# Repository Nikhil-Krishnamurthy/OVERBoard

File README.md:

# OVERBoard
This is my attempt at creating a custom keyboard with several unique features, this has a layer system that I have modified to work with specific tasks on my pc, I also have a 2.8 in screen to display custom text, ui, and macros. There is a full 78 led matrix, dual pi pico system, and 3 rotary encoders that interface in this system.   
# Key Features   
Full TKL Keyboard Matrix   
4 Layer Keyboard System   
3 Encoders Interfacing with the Layer System   
78 Led Matrix system   
320 x 240 2.8 inch display   
Custom UI and layer switching menus   
Computer interface and data transmission   
Custom 5A power system   

## Onshape-link:
https://cad.onshape.com/documents/a6bd6c4e9013194f1dc31777/w/de360b55982ee6c60ca7c4d4/e/a374dba059f4ceb7d8e6600d?renderMode=0&uiState=6a4a7855afac9a027952f82f 

# Flashing      
Flashing is done through two steps, compiling the C qmk file through QMK MSYS to compile to a uf2 file, which then can be flashed to the pi pico through holding the bootsel button and plugging it in to the usb power. Then just upload the new uf2 file to the pi pico. To flash the pi pico 2 for the display, you have to download the entire folder of the custom c++, and then through a terminal of your choice compile it. (I use vs code and i got it to work through there, idk about others). Then upload the second uf2 file to the pi pico 2 by holding the bootsel button and uploading it there.

# BOM   
78 [3 Pin Mechanical Keyboard Switches   ](https://www.amazon.com/Leezmark-Mechanical-Dustproof-Replacement-Keyboards/dp/B0GV78B48N/ref=mp_s_a_1_20_sspa?crid=2GGAVKPX5GKH&dib=eyJ2IjoiMSJ9.BS9ZW8A40QZK6iI4UmdZkYcVp812RDtM8dzqQtxJq5kz5jddC0aGCLYpUDj6oWZM4geYAz7LL5dJKQJ_sMRCqYbuT9Zwzy20VnrTvVNVI-2PMGM8y_OT_gXPSKltVj0ZCmtBrzLAvtF8hVyPpS-bcG8HSGX4meJ7BWVw4GwyFBtzq-VV4k_-OB3_U29mYmabBNX5P_2u1xLUz0WsYM_SZg.sOaHXiIPD6Bd4c6RHFdcsiI9AAYZXd1oFGZit3XfvzE&dib_tag=se&keywords=mechanical+keyboard+switches&qid=1786102391&sprefix=mecha%2Caps%2C1667&sr=8-20-spons&xpid=P4xuzyhmO1Kis&sp_csd=d2lkZ2V0TmFtZT1zcF9waG9uZV9zZWFyY2hfbXRm&psc=1)   
78 [SK6812 Mini-E LEDs](https://www.amazon.com/Lizusidtsy-Similar-Individually-Addressable-500076361/dp/B0D62PYX62/ref=mp_s_a_1_10?crid=1HXPOB1FA28BI&dib=eyJ2IjoiMSJ9.9VtPip6eaOO1-XFGgh2XxRcv7goQ3zQpYu2U5s9L9nSHVgE9buEYKNyEW3iah_ciC9jxtcFWsezkLg6mPwawYLvC0YwcBautoxVQw8uHIajIIKaw2BAEOz0msTKg2i1JiFDcOfpwOktIFD5m-rM-sLH5aurg7jONQpTc9ztb7qjGY4VW4UKlHhBSvXDKLMnpFN1p0uSk9QlHmR1fMhQoKQ.cp7zFL1gJURH3RVmt4PrTOWDThkTRaVYkx8k7CsSdDU&dib_tag=se&keywords=sk6812+mini+e&qid=1786102738&s=industrial&sprefix=sk6812+mini+e%2Cindustrial%2C227&sr=1-10-catcorr)   
3 [EC11 Rotary encoders](https://www.amazon.com/CGNRONEAU-Potentiometer-Raspberry-Electronics-Projects/dp/B0G48Z8B9Q/ref=mp_s_a_1_5?crid=SJZ3ZTB60ZB5&dib=eyJ2IjoiMSJ9.DXj00Da7o69UiffMrM5wQRPYTBTu96F7xG_REVVFTXyDDE7Ct_VRsisag9rFMKgkTnHD1maKyGOHqHwwsa9QOm4nJbuxf-u1h8I8Xeu_QS-_GGyZhZ7IW7rUedH8wyPUQpJnUpBYRTrw7qkoa3L6uI7fxGQ1JdWoYiTZq1MJnh7YbKwp_SVgYWuv54q8JgQ_uJAa0EScvo-vtg_HxxVShA.oFRLtfeS884kGRJ9817n1MkEJusgqgWJDlI8D6AScFo&dib_tag=se&keywords=ec11+rotary+encoder&qid=1786102850&s=industrial&sprefix=ec11+rotary+encoder%2Cindustrial%2C296&sr=1-5)    
1 [Keycap Set](https://www.amazon.com/Womier-Doubleshot-Universal-Compatiability-Switches/dp/B0DD3MFZJH/ref=mp_s_a_1_4?dib=eyJ2IjoiMSJ9.NYb-M_oBXZ4sYXBFeumxLCGVNsY9r-6v4MP0X_NiII59u2l-eoBS-fSIwKjgQw8UQnKp5aItpglhW1_vmJ5Zi3Ai9TdxAWYqoLRUdImCShzhl38JPSy1eJCwtC9gqwE5WcnlIVPYZwyoVEbIaEuOxTBP47_ipk5BJsu7sIIcEQwtiRsUoIT2AKQ4hwcLJanAgVfd3swCPsz1cHzkkB3fEA.LHY6OJX_2Vt0jXq0Am2Od0HAyrY-O1Iw68TDGDFU8LQ&dib_tag=se&keywords=keycap+set&qid=1786102952&sr=8-4)   
1 [Stabilizer Set](https://www.amazon.com/DUROCK-Stabilizers-Translucent-Keyboard-Mechanical/dp/B0B2RVN19F/ref=mp_s_a_1_1?crid=RUCGVW5PCSL7&dib=eyJ2IjoiMSJ9.FUE_jABwKLA1OASEMhZRJdxEw5T6Pmde5A4peNgmaHbFq5e1Nyw0ducx_W87F-YdPvY6Z0F0Ws9Z5KWRT10otnbc7i3mqQ-KSsT8q0_UoKFDrMQOU2Zr7UFsQVD8SH_3jzvns1ANBC4ikHp7kZKjsS9mrpaVKSuOX6QgBT75oK6L6rT38cDrAPZf1bMy2eiDNbRMvr3UK6Jnu7D304s7ww.Ds4MVNaTUXEreelnZ5y9dkQEI_1UVwucidZDuxVlDSo&dib_tag=se&keywords=keyboard+stabilizer+pcb+mount&qid=1786103068&sprefix=keyboard+stabilizer+pcb+moun%2Cpc%2C281&sr=8-1)   
10 [0.1uF SMD 0805 Capacitors](https://www.digikey.com/en/products/detail/samsung-electro-mechanics/CL21B104KBCNNNC/3886661)   
2 [10uF SMD 1206 Capacitors](https://www.digikey.com/en/products/detail/taiyo-yuden/TMK316BJ106ML-T/1172143)   
83 [Through Hole Diodes](https://www.digikey.com/en/products/detail/onsemi/1N4148TR/458811)   
1 [Raspberry Pi Pico](https://www.digikey.com/en/products/detail/raspberry-pi/SC0915/13624793)   
1 [Raspberry Pi Pico 2](https://www.digikey.com/en/products/detail/raspberry-pi/SC1631/24627136)   
1 [SN74HCT245PWR](https://www.digikey.com/en/products/detail/texas-instruments/SN74HCT245PWR/376998)   
1 [Mini 560 5A 5V](https://www.amazon.com/ACEIRMC-Efficiency-Converter-Regulator-Stabilized/dp/B0C98GN9R5/ref=mp_s_a_1_4?crid=2AVG7EVJEY2B9&dib=eyJ2IjoiMSJ9.YQJnYbrVm2KfCwo1WAsOv_9mCXY0p27qXY_bAWcHnAztXAalke-6x_LLhC_8PmYHInSFxohDrh9t3UeH3i8bvUFj-epQ0_xXJwlrhhlWOhZJfog3TIgcDjFTwO7dwkMsRUWsBu6tSt_Lye0NUieFGLgw9ekInTt2RbwoX9bJ0JOObYWOKjC2M1PCHkkIN_Ke.J03En0j60RIf0zi2gOz474K4xhu8YiPPLa1dOAJTqoU&dib_tag=se&keywords=mini+560+5v+5a&qid=1786103755&sprefix=mi%2Cpc%2C4329&sr=8-4)   
1 [Adafruit 5807 Power Evaluation Board](https://www.digikey.com/en/products/detail/adafruit-industries-llc/5807/21839778)   
1 [2.8 in 320 x 240 SPI Serial TFT display](https://www.amazon.com/DIANN-ILI9341-Display-320x240-Screen/dp/B0BNQBKFCT/ref=mp_s_a_1_4?crid=1IO0JMISFCIW5&dib=eyJ2IjoiMSJ9.QdQv9Z60xKItFJyKtGDGVEe0E5DZHOpvSyDlzSsJM0ahxq3n0oBPRCWegDN5Bh4kMcEsYOjRE9r_6PQ-nRDFi45yabmboblZpYIfpVL-1wZ9Gbc-wRBgY9Q3zt3W4nQNGskA3h3qFBMzfNfbmmOG4S9Yv8aLMXAZH_x-N28DwhMUSRzU2xY8tLeu3uxt2kHptwfZuykGqU6NKyFsdJm3gw.irWclV9rp7JxQy7JeD-LQJ3wXUPrGnMFIF87TexXEg0&dib_tag=se&keywords=2.8+in+spi+display+color&qid=1786105121&s=industrial&sprefix=2.8+in+spi+display+color%2Cindustrial%2C196&sr=1-4)   
2 [PTS810_SJM_250](https://www.digikey.com/en/products/detail/c-k/PTS810SJK250SMTR-LFS/4176611)   
2 [4.7k SMD 0805 resistors](https://www.digikey.com/en/products/detail/panasonic-industry/ERA-6AEB472V/1465765)    
10 [10k SMD 0805 resistors](https://www.digikey.com/en/products/detail/stackpole-electronics-inc/RMCF0805FT10K0/1760676)   
## Extra Parts not part of BOM
9 [M3 Heat set inserts](https://www.amazon.com/HANGLIFE-Heat-Set-Threaded-Printing-Components/dp/B0CS6VZYL8/ref=mp_s_a_1_2_sspa?crid=2B6EZ44CM5F8W&dib=eyJ2IjoiMSJ9.64CwhAq2F4wt2J7X2RWpxsbGQNoHV8siDt0bl6JQWF52xU_4RhH0jdpfO7SRVfnWZU2jv3CI10a2JeWKff2m2wFIr10td08-ZNDs7jlZM_gW5mSgs-W56Qb0sIpuTAgPvamIXJbOre0ZmTZ6kXSKiIbGKsS7vC-VFf2Imqp2yVl_mDHaTy5djVOZQ_dIL6f3OuER50SkQsIQripMtAXk4A.KM8dXGX0d71WWG7ur53YMH8J9nQ2REom7eKTVHaXpUI&dib_tag=se&keywords=m3+heat+set+inserts&qid=1786105506&s=industrial&sprefix=m3+heat+s%2Cindustrial%2C246&sr=1-2-spons&sp_csd=d2lkZ2V0TmFtZT1zcF9waG9uZV9zZWFyY2hfYXRm&psc=1)   
9 [M3 Screws](https://www.amazon.com/Fgruh-750PCS-Assortment-Washers-Assorted/dp/B0FGV5FCBN/ref=mp_s_a_1_1_sspa?crid=1ZGG85P77CJCY&dib=eyJ2IjoiMSJ9.cPekTjkEYdRojQiPp36UK-D0OriKRZ1Tcz-iYae4l8YfNDd_5vroqMqjPyDoD8r98dxg69F8Q4x7A4Qg04ZpZkq3-5Vz_8pzyy0ST4oyfjEEufYmdOm-INr8fJD5TDph9qhOa-j-fmcB0ADX9T1tIyiP6yaLBkyUwThoKVBjPId_kiXSb0qIrofmAIKtf7pJRZK1cPMjvmaWqAiZ1AKcZg.GNyAzvliKQY6RL9mJRsNCAE3UinRfEleG_EmtBRQXtc&dib_tag=se&keywords=m3+screws&qid=1786105661&s=industrial&sprefix=m3+screws%2Cindustrial%2C256&sr=1-1-spons&sp_csd=d2lkZ2V0TmFtZT1zcF9waG9uZV9zZWFyY2hfYXRm&psc=1)   
2 [M2.5 Heat Set Inserts](https://www.amazon.com/HANGLIFE-Heat-Set-Threaded-Printing-Components/dp/B0CS6YVJYD/ref=mp_s_a_1_2_sspa?crid=2B6EZ44CM5F8W&dib=eyJ2IjoiMSJ9.64CwhAq2F4wt2J7X2RWpxsbGQNoHV8siDt0bl6JQWF52xU_4RhH0jdpfO7SRVfnWZU2jv3CI10a2JeWKff2m2wFIr10td08-ZNDs7jlZM_gW5mSgs-W56Qb0sIpuTAgPvamIXJbOre0ZmTZ6kXSKiIbGKsS7vC-VFf2Imqp2yVl_mDHaTy5djVOZQ_dIL6f3OuER50SkQsIQripMtAXk4A.KM8dXGX0d71WWG7ur53YMH8J9nQ2REom7eKTVHaXpUI&dib_tag=se&keywords=m3%2Bheat%2Bset%2Binserts&qid=1786105506&s=industrial&sprefix=m3%2Bheat%2Bs%2Cindustrial%2C246&sr=1-2-spons&sp_csd=d2lkZ2V0TmFtZT1zcF9waG9uZV9zZWFyY2hfYXRm&psc=1&th=1)   
2 [M2.5 Screws](https://www.amazon.com/Fgruh-750PCS-Assortment-Washers-Assorted/dp/B0FG2BYJSR/ref=mp_s_a_1_1_sspa?crid=1ZGG85P77CJCY&dib=eyJ2IjoiMSJ9.cPekTjkEYdRojQiPp36UK-D0OriKRZ1Tcz-iYae4l8YfNDd_5vroqMqjPyDoD8r98dxg69F8Q4x7A4Qg04ZpZkq3-5Vz_8pzyy0ST4oyfjEEufYmdOm-INr8fJD5TDph9qhOa-j-fmcB0ADX9T1tIyiP6yaLBkyUwThoKVBjPId_kiXSb0qIrofmAIKtf7pJRZK1cPMjvmaWqAiZ1AKcZg.GNyAzvliKQY6RL9mJRsNCAE3UinRfEleG_EmtBRQXtc&dib_tag=se&keywords=m3%2Bscrews&qid=1786105661&s=industrial&sprefix=m3%2Bscrews%2Cindustrial%2C256&sr=1-1-spons&sp_csd=d2lkZ2V0TmFtZT1zcF9waG9uZV9zZWFyY2hfYXRm&psc=1&th=1)   
1 [1Kg Matte Black Filament](https://www.amazon.com/ELEGOO-Filament-Dimensional-Accuracy-Carboard/dp/B0CFV3WF7P/ref=mp_s_a_1_1_sspa?crid=2WGHGADYDSPZ3&dib=eyJ2IjoiMSJ9.jj4FdZs0k5Gj9BMVFw2sIqMRLoQnKg6Dh9C_efasYCNLHC9B4MPcdiQZZ9ZXBsrlR_gga4llJi5TY_AL7se-jTgKuxSOclNDDB5CvK38oBG-ydVc6MiEftwGY9kheukIrHDEPPKRb3bsytmUJS91ZC5HKMM_KCdLlz8CiN8cHiQ8tEZizCX_oA0306VRSqZExDdBiODIV9xqZQAQjvHG-Q.TCRhgAn-7mqXjFZFVEeZ7ere4YNhtVbXsh61Izosbp4&dib_tag=se&keywords=matte+black+pla&qid=1786105829&s=industrial&sprefix=matte+black+pla%2Cindustrial%2C248&sr=1-1-spons&sp_csd=d2lkZ2V0TmFtZT1zcF9waG9uZV9zZWFyY2hfYXRm&psc=1)   
## PCB    
1 Custom Pcb    
## BOM as CSV Format    
[BOM.csv](https://github.com/Nikhil-Krishnamurthy/OVERBoard/blob/main/BOM.csv)     

# Full Render:    

# Schematic:   

# PCB:

# CAD:

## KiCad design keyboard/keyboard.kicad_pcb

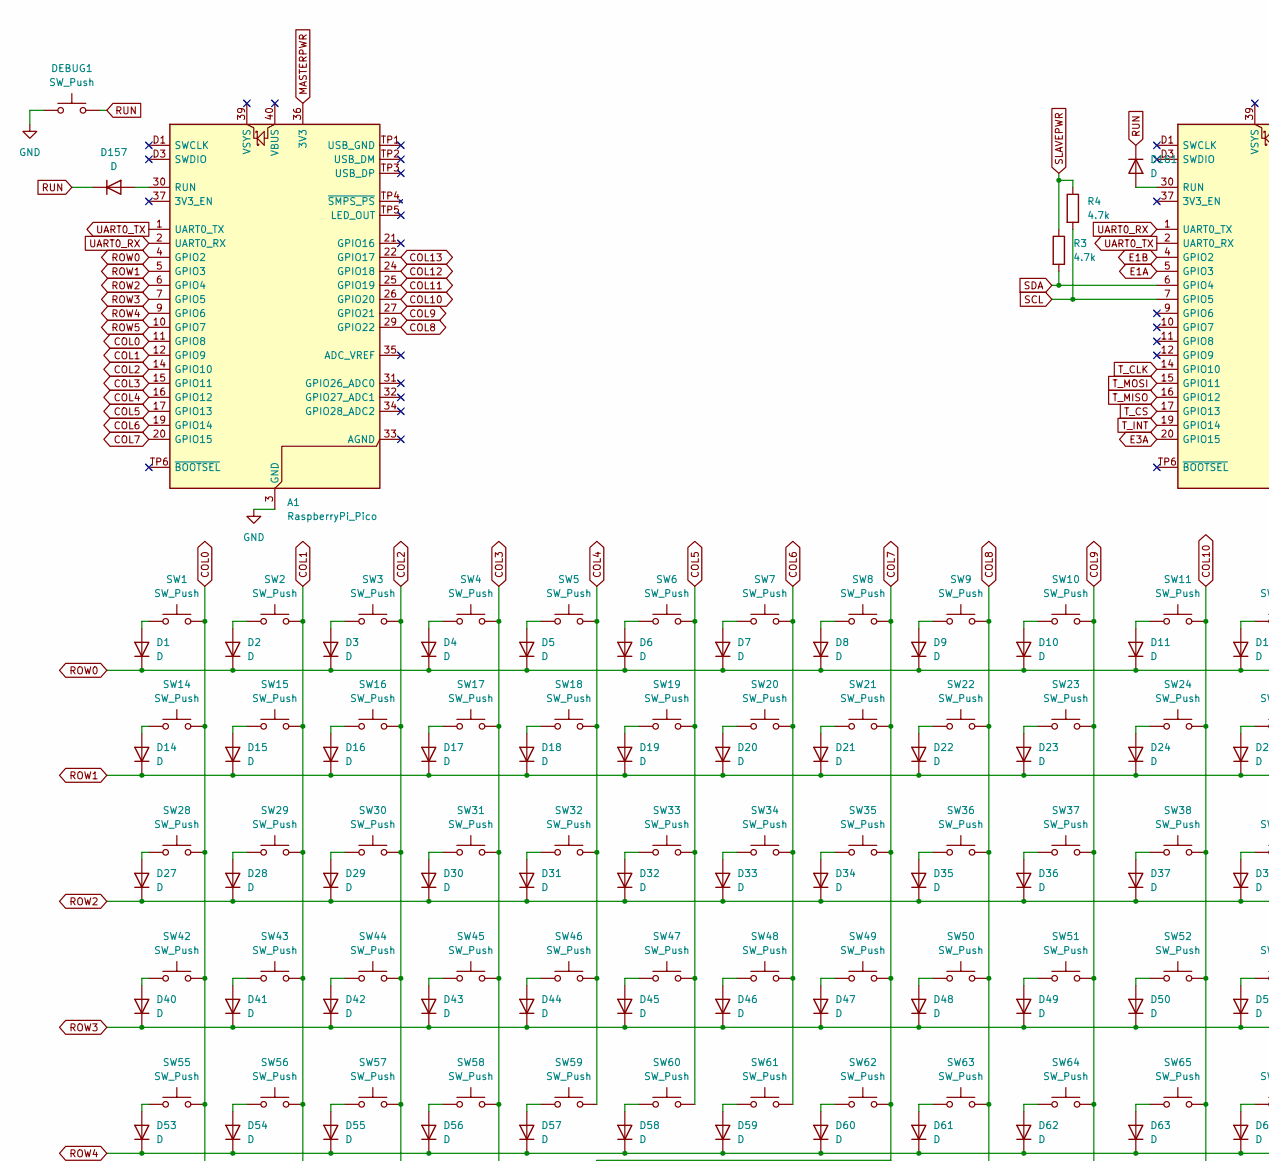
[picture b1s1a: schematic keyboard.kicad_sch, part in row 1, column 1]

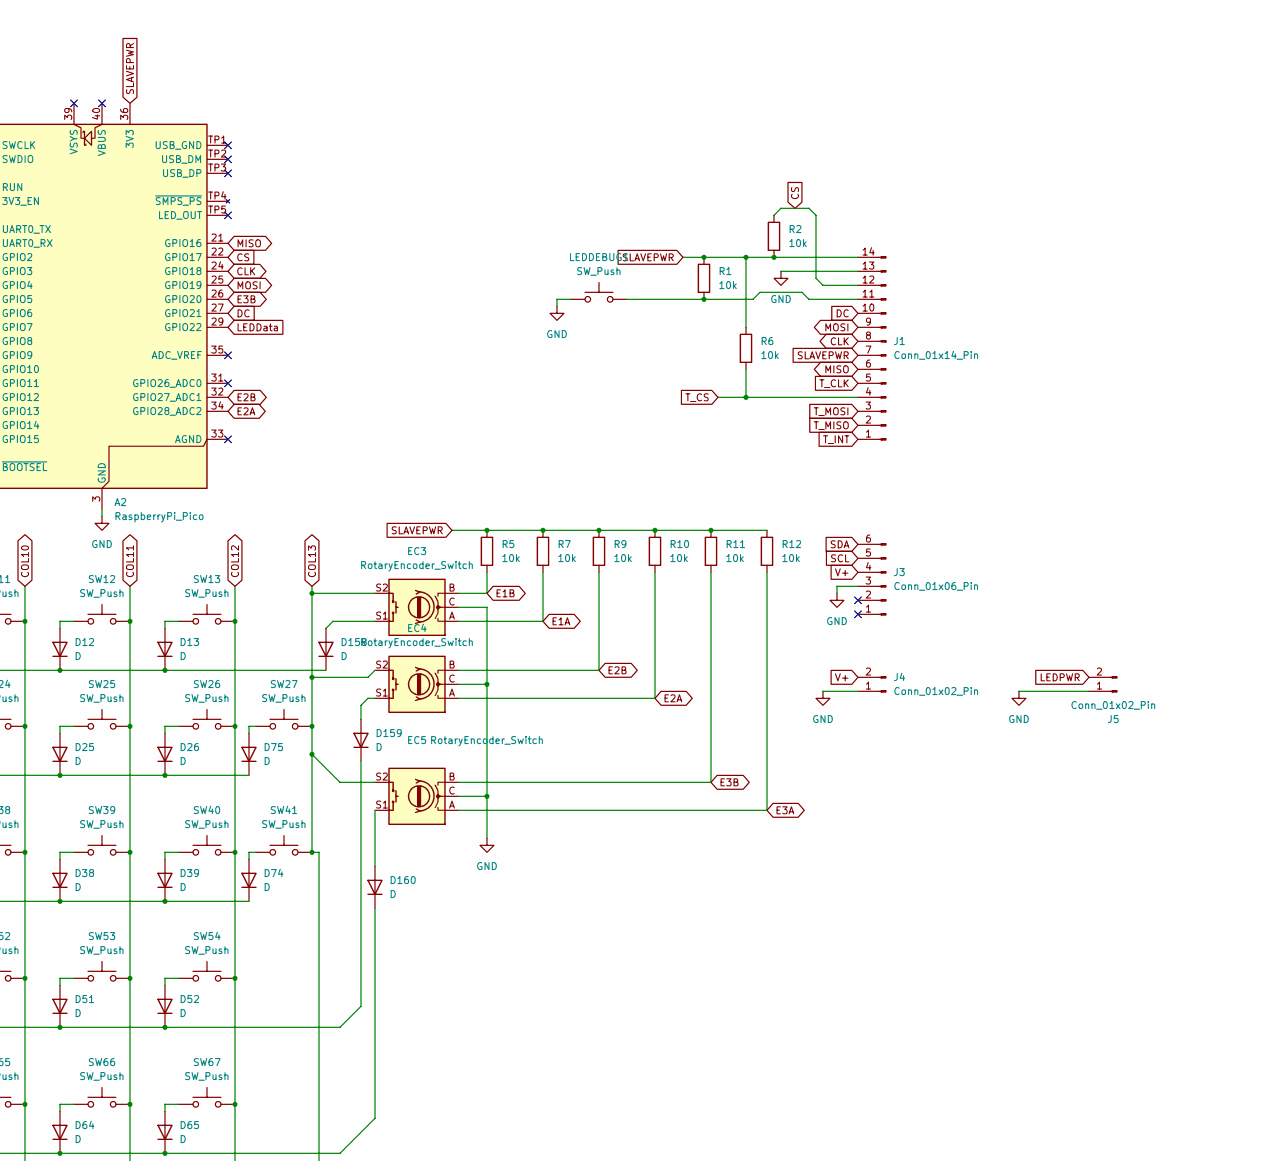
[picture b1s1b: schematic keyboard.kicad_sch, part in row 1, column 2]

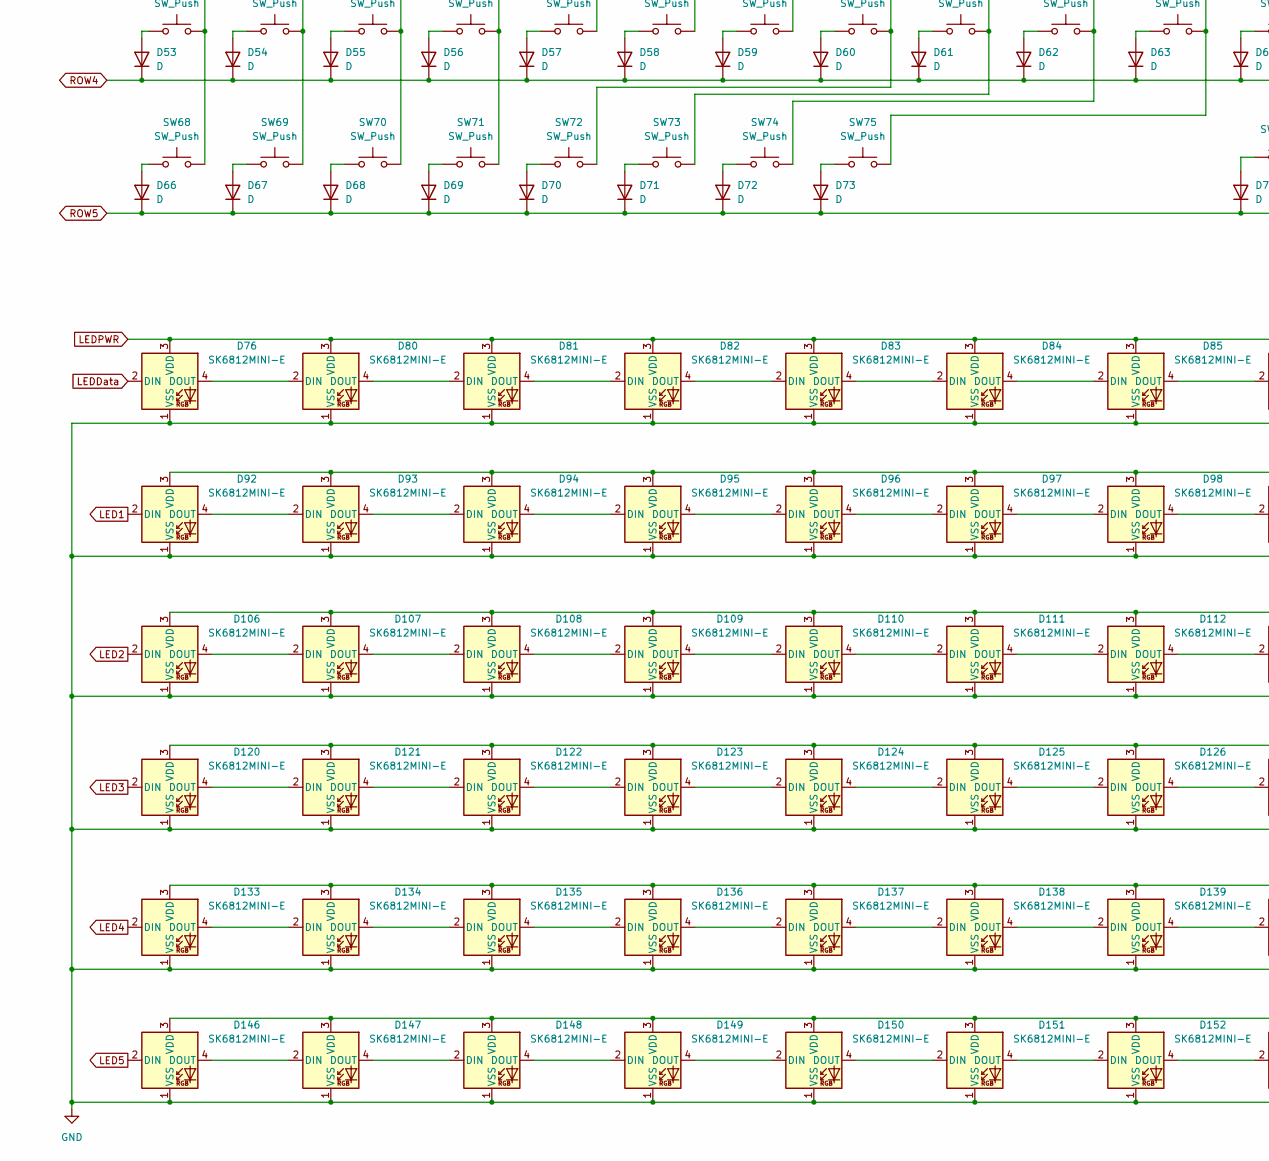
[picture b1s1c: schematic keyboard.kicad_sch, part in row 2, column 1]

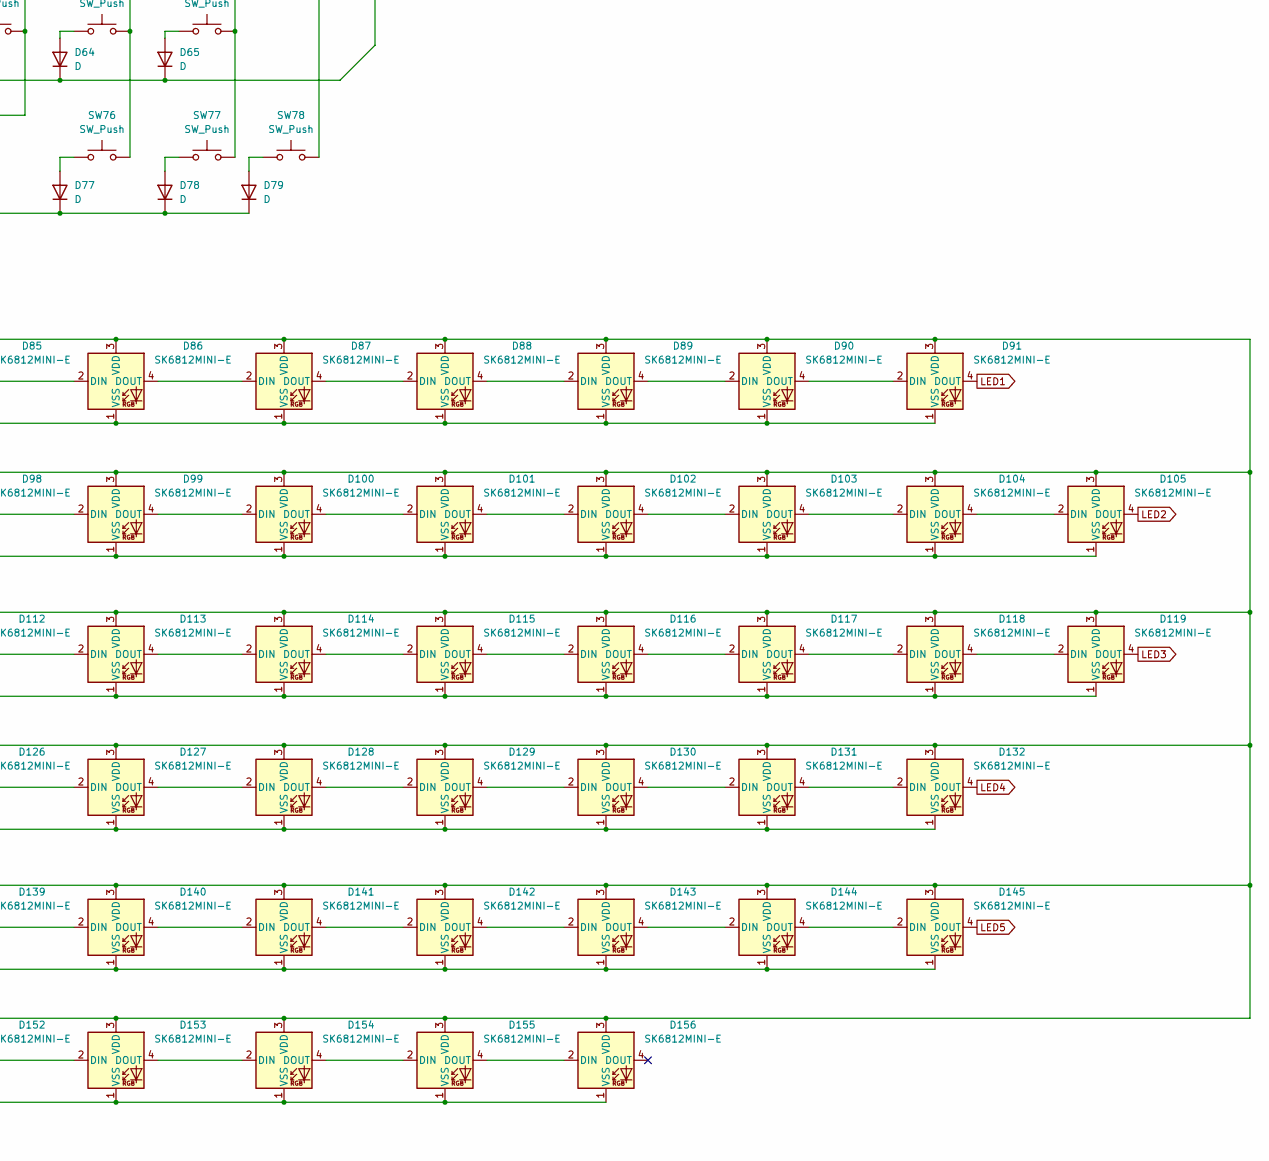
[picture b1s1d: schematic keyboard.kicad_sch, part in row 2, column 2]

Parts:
A1, A2: RaspberryPi_Pico; RaspberryPi_Pico_Common_THT
D1, D2, D3, D4, D5, D6, D7, D8, D9, D10, D11, D12, D13, D14, D15, D16, D17, D18, D19, D20, D21, D22, D23, D24, D25, D26, D27, D28, D29, D30, D31, D32, D33, D34, D35, D36, D37, D38, D39, D40, D41, D42, D43, D44, D45, D46, D47, D48, D49, D50, D51, D52, D53, D54, D55, D56, D57, D58, D59, D60, D61, D62, D63, D64, D65, D66, D67, D68, D69, D70, D71, D72, D73, D74, D75, D77, D78, D79, D157, D158, D159, D160, D161: D; D_DO-35_SOD27_P7.62mm_Horizontal
D76, D80, D81, D82, D83, D84, D85, D86, D87, D88, D89, D90, D91, D92, D93, D94, D95, D96, D97, D98, D99, D100, D101, D102, D103, D104, D105, D106, D107, D108, D109, D110, D111, D112, D113, D114, D115, D116, D117, D118, D119, D120, D121, D122, D123, D124, D125, D126, D127, D128, D129, D130, D131, D132, D133, D134, D135, D136, D137, D138, D139, D140, D141, D142, D143, D144, D145, D146, D147, D148, D149, D150, D151, D152, D153, D154, D155, D156: SK6812MINI-E; LED_SK6812MINI-E_3.2x2.8mm_P1.5mm_ReverseMount
DEBUG1: SW_Push; SW_PTS810_SJM_250_SMTR_LFS
EC3, EC4, EC5: RotaryEncoder_Switch; RotaryEncoder_Alps_EC11E-Switch_Vertical_H20mm
J1: Conn_01x14_Pin; PinHeader_1x14_P2.54mm_Vertical
J3: Conn_01x06_Pin; PinHeader_1x06_P2.54mm_Vertical
J4, J5: Conn_01x02_Pin; PinHeader_1x02_P2.54mm_Vertical
LEDDEBUG1: SW_Push; SW_PTS810_SJM_250_SMTR_LFS
R1, R2, R5, R6, R7, R9, R10, R11, R12: 10k; R_0805_2012Metric_Pad1.20x1.40mm_HandSolder
R3, R4: 4.7k; R_0805_2012Metric_Pad1.20x1.40mm_HandSolder
SW1, SW2, SW3, SW4, SW5, SW6, SW7, SW8, SW9, SW10, SW11, SW12, SW13, SW14, SW15, SW16, SW17, SW18, SW19, SW20, SW21, SW22, SW23, SW24, SW25, SW26, SW29, SW30, SW31, SW32, SW33, SW34, SW35, SW36, SW37, SW38, SW39, SW40, SW43, SW44, SW45, SW46, SW47, SW48, SW49, SW50, SW51, SW52, SW53, SW56, SW57, SW58, SW59, SW60, SW61, SW62, SW63, SW64, SW65, SW67, SW76, SW77, SW78: SW_Push; SW_Cherry_MX_1.00u_PCB
SW27: SW_Push; SW_Cherry_MX_2.00u_PCB
SW28, SW41, SW42: SW_Push; SW_Cherry_MX_1.50u_PCB
SW54, SW55: SW_Push; SW_Cherry_MX_2.25u_PCB
SW66: SW_Push; SW_Cherry_MX_2.75u_PCB
SW68, SW69, SW70, SW72, SW73, SW74, SW75: SW_Push; SW_Cherry_MX_1.25u_PCB
SW71: SW_Push; SW_Cherry_MX_6.25u_PCB

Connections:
CLK: A2.24 (GPIO18), J1.8
COL0: A1.11 (GPIO8), SW1.2, SW14.2, SW28.2, SW42.2, SW55.2, SW68.2
COL1: A1.12 (GPIO9), SW2.2, SW15.2, SW29.2, SW43.2, SW56.2, SW69.2
COL2: A1.14 (GPIO10), SW3.2, SW16.2, SW30.2, SW44.2, SW57.2, SW70.2
COL3: A1.15 (GPIO11), SW4.2, SW17.2, SW31.2, SW45.2, SW58.2, SW71.2
COL4: A1.16 (GPIO12), SW5.2, SW18.2, SW32.2, SW46.2, SW59.2
COL5: A1.17 (GPIO13), SW6.2, SW19.2, SW33.2, SW47.2, SW60.2
COL6: A1.19 (GPIO14), SW7.2, SW20.2, SW34.2, SW48.2, SW61.2
COL7: A1.20 (GPIO15), SW8.2, SW21.2, SW35.2, SW49.2, SW62.2, SW72.2
COL8: A1.29 (GPIO22), SW9.2, SW22.2, SW36.2, SW50.2, SW63.2, SW73.2
COL9: A1.27 (GPIO21), SW10.2, SW23.2, SW37.2, SW51.2, SW64.2, SW74.2
COL10: A1.26 (GPIO20), SW11.2, SW24.2, SW38.2, SW52.2, SW65.2, SW75.2
COL11: A1.25 (GPIO19), SW12.2, SW25.2, SW39.2, SW53.2, SW66.2, SW76.2
COL12: A1.24 (GPIO18), SW13.2, SW26.2, SW40.2, SW54.2, SW67.2, SW77.2
COL13: A1.22 (GPIO17), EC3.S2, EC4.S2, EC5.S2, SW27.2, SW41.2, SW78.2
CS: A2.22 (GPIO17), J1.12, R2.1
DC: A2.27 (GPIO21), J1.10
E1A: A2.5 (GPIO3), EC3.A, R7.2
E1B: A2.4 (GPIO2), EC3.B, R5.2
E2A: A2.34 (GPIO28_ADC2), EC4.A, R10.2
E2B: A2.32 (GPIO27_ADC1), EC4.B, R9.2
E3A: A2.20 (GPIO15), EC5.A, R12.2
E3B: A2.26 (GPIO20), EC5.B, R11.2
GND: A1.3 (GND), A1.8 (GND), A1.13 (GND), A1.18 (GND), A1.23 (GND), A1.28 (GND), A1.38 (GND), A1.D2 (GND), A2.3 (GND), A2.8 (GND), A2.13 (GND), A2.18 (GND), A2.23 (GND), A2.28 (GND), A2.38 (GND), A2.D2 (GND), D76.1 (VSS), D80.1 (VSS), D81.1 (VSS), D82.1 (VSS), D83.1 (VSS), D84.1 (VSS), D85.1 (VSS), D86.1 (VSS), D87.1 (VSS), D88.1 (VSS), D89.1 (VSS), D90.1 (VSS), D91.1 (VSS), D92.1 (VSS), D93.1 (VSS), D94.1 (VSS), D95.1 (VSS), D96.1 (VSS), D97.1 (VSS), D98.1 (VSS), D99.1 (VSS), D100.1 (VSS), D101.1 (VSS), D102.1 (VSS), D103.1 (VSS), D104.1 (VSS), D105.1 (VSS), D106.1 (VSS), D107.1 (VSS), D108.1 (VSS), D109.1 (VSS), D110.1 (VSS), D111.1 (VSS), D112.1 (VSS), D113.1 (VSS), D114.1 (VSS), D115.1 (VSS), D116.1 (VSS), D117.1 (VSS), D118.1 (VSS), D119.1 (VSS), D120.1 (VSS), D121.1 (VSS), D122.1 (VSS), D123.1 (VSS), D124.1 (VSS), D125.1 (VSS), D126.1 (VSS), D127.1 (VSS), D128.1 (VSS), D129.1 (VSS), D130.1 (VSS), D131.1 (VSS), D132.1 (VSS), D133.1 (VSS), D134.1 (VSS), D135.1 (VSS), D136.1 (VSS), D137.1 (VSS), D138.1 (VSS), D139.1 (VSS), D140.1 (VSS), D141.1 (VSS), D142.1 (VSS), D143.1 (VSS), D144.1 (VSS), D145.1 (VSS), D146.1 (VSS), D147.1 (VSS), D148.1 (VSS), D149.1 (VSS), D150.1 (VSS), D151.1 (VSS), D152.1 (VSS), D153.1 (VSS), D154.1 (VSS), D155.1 (VSS), D156.1 (VSS), DEBUG1.1, EC3.C, EC4.C, EC5.C, J1.13, J3.3, J4.1, J5.1, LEDDEBUG1.1
LED1: D91.4 (DOUT), D92.2 (DIN)
LED2: D105.4 (DOUT), D106.2 (DIN)
LED3: D119.4 (DOUT), D120.2 (DIN)
LED4: D132.4 (DOUT), D133.2 (DIN)
LED5: D145.4 (DOUT), D146.2 (DIN)
LEDData: A2.29 (GPIO22), D76.2 (DIN)
LEDPWR: D76.3 (VDD), D80.3 (VDD), D81.3 (VDD), D82.3 (VDD), D83.3 (VDD), D84.3 (VDD), D85.3 (VDD), D86.3 (VDD), D87.3 (VDD), D88.3 (VDD), D89.3 (VDD), D90.3 (VDD), D91.3 (VDD), D92.3 (VDD), D93.3 (VDD), D94.3 (VDD), D95.3 (VDD), D96.3 (VDD), D97.3 (VDD), D98.3 (VDD), D99.3 (VDD), D100.3 (VDD), D101.3 (VDD), D102.3 (VDD), D103.3 (VDD), D104.3 (VDD), D105.3 (VDD), D106.3 (VDD), D107.3 (VDD), D108.3 (VDD), D109.3 (VDD), D110.3 (VDD), D111.3 (VDD), D112.3 (VDD), D113.3 (VDD), D114.3 (VDD), D115.3 (VDD), D116.3 (VDD), D117.3 (VDD), D118.3 (VDD), D119.3 (VDD), D120.3 (VDD), D121.3 (VDD), D122.3 (VDD), D123.3 (VDD), D124.3 (VDD), D125.3 (VDD), D126.3 (VDD), D127.3 (VDD), D128.3 (VDD), D129.3 (VDD), D130.3 (VDD), D131.3 (VDD), D132.3 (VDD), D133.3 (VDD), D134.3 (VDD), D135.3 (VDD), D136.3 (VDD), D137.3 (VDD), D138.3 (VDD), D139.3 (VDD), D140.3 (VDD), D141.3 (VDD), D142.3 (VDD), D143.3 (VDD), D144.3 (VDD), D145.3 (VDD), D146.3 (VDD), D147.3 (VDD), D148.3 (VDD), D149.3 (VDD), D150.3 (VDD), D151.3 (VDD), D152.3 (VDD), D153.3 (VDD), D154.3 (VDD), D155.3 (VDD), D156.3 (VDD), J5.2
MASTERPWR: A1.36 (3V3)
MISO: A2.21 (GPIO16), J1.6
MOSI: A2.25 (GPIO19), J1.9
unnamed: A1.30 (RUN), D157.2 (A)
unnamed: A2.30 (RUN), D161.2 (A)
unnamed: D1.2 (A), SW1.1
unnamed: D2.2 (A), SW2.1
unnamed: D3.2 (A), SW3.1
unnamed: D4.2 (A), SW4.1
unnamed: D5.2 (A), SW5.1
unnamed: D6.2 (A), SW6.1
unnamed: D7.2 (A), SW7.1
unnamed: D8.2 (A), SW8.1
unnamed: D9.2 (A), SW9.1
unnamed: D10.2 (A), SW10.1
unnamed: D11.2 (A), SW11.1
unnamed: D12.2 (A), SW12.1
unnamed: D13.2 (A), SW13.1
unnamed: D14.2 (A), SW14.1
unnamed: D15.2 (A), SW15.1
unnamed: D16.2 (A), SW16.1
unnamed: D17.2 (A), SW17.1
unnamed: D18.2 (A), SW18.1
unnamed: D19.2 (A), SW19.1
unnamed: D20.2 (A), SW20.1
unnamed: D21.2 (A), SW21.1
unnamed: D22.2 (A), SW22.1
unnamed: D23.2 (A), SW23.1
unnamed: D24.2 (A), SW24.1
unnamed: D25.2 (A), SW25.1
unnamed: D26.2 (A), SW26.1
unnamed: D27.2 (A), SW28.1
unnamed: D28.2 (A), SW29.1
unnamed: D29.2 (A), SW30.1
unnamed: D30.2 (A), SW31.1
unnamed: D31.2 (A), SW32.1
unnamed: D32.2 (A), SW33.1
unnamed: D33.2 (A), SW34.1
unnamed: D34.2 (A), SW35.1
unnamed: D35.2 (A), SW36.1
unnamed: D36.2 (A), SW37.1
unnamed: D37.2 (A), SW38.1
unnamed: D38.2 (A), SW39.1
unnamed: D39.2 (A), SW40.1
unnamed: D40.2 (A), SW42.1
unnamed: D41.2 (A), SW43.1
unnamed: D42.2 (A), SW44.1
unnamed: D43.2 (A), SW45.1
unnamed: D44.2 (A), SW46.1
unnamed: D45.2 (A), SW47.1
unnamed: D46.2 (A), SW48.1
unnamed: D47.2 (A), SW49.1
unnamed: D48.2 (A), SW50.1
unnamed: D49.2 (A), SW51.1
unnamed: D50.2 (A), SW52.1
unnamed: D51.2 (A), SW53.1
unnamed: D52.2 (A), SW54.1
unnamed: D53.2 (A), SW55.1
unnamed: D54.2 (A), SW56.1
unnamed: D55.2 (A), SW57.1
unnamed: D56.2 (A), SW58.1
unnamed: D57.2 (A), SW59.1
unnamed: D58.2 (A), SW60.1
unnamed: D59.2 (A), SW61.1
unnamed: D60.2 (A), SW62.1
unnamed: D61.2 (A), SW63.1
unnamed: D62.2 (A), SW64.1
unnamed: D63.2 (A), SW65.1
unnamed: D64.2 (A), SW66.1
unnamed: D65.2 (A), SW67.1
unnamed: D66.2 (A), SW68.1
unnamed: D67.2 (A), SW69.1
unnamed: D68.2 (A), SW70.1
unnamed: D69.2 (A), SW71.1
unnamed: D70.2 (A), SW72.1
unnamed: D71.2 (A), SW73.1
unnamed: D72.2 (A), SW74.1
unnamed: D73.2 (A), SW75.1
unnamed: D74.2 (A), SW41.1
unnamed: D75.2 (A), SW27.1
unnamed: D76.4 (DOUT), D80.2 (DIN)
unnamed: D77.2 (A), SW76.1
unnamed: D78.2 (A), SW77.1
unnamed: D79.2 (A), SW78.1
unnamed: D80.4 (DOUT), D81.2 (DIN)
unnamed: D81.4 (DOUT), D82.2 (DIN)
unnamed: D82.4 (DOUT), D83.2 (DIN)
unnamed: D83.4 (DOUT), D84.2 (DIN)
unnamed: D84.4 (DOUT), D85.2 (DIN)
unnamed: D85.4 (DOUT), D86.2 (DIN)
unnamed: D86.4 (DOUT), D87.2 (DIN)
unnamed: D87.4 (DOUT), D88.2 (DIN)
unnamed: D88.4 (DOUT), D89.2 (DIN)
unnamed: D89.4 (DOUT), D90.2 (DIN)
unnamed: D90.4 (DOUT), D91.2 (DIN)
unnamed: D92.4 (DOUT), D93.2 (DIN)
unnamed: D93.4 (DOUT), D94.2 (DIN)
unnamed: D94.4 (DOUT), D95.2 (DIN)
unnamed: D95.4 (DOUT), D96.2 (DIN)
unnamed: D96.4 (DOUT), D97.2 (DIN)
unnamed: D97.4 (DOUT), D98.2 (DIN)
unnamed: D98.4 (DOUT), D99.2 (DIN)
unnamed: D99.4 (DOUT), D100.2 (DIN)
unnamed: D100.4 (DOUT), D101.2 (DIN)
unnamed: D101.4 (DOUT), D102.2 (DIN)
unnamed: D102.4 (DOUT), D103.2 (DIN)
unnamed: D103.4 (DOUT), D104.2 (DIN)
unnamed: D104.4 (DOUT), D105.2 (DIN)
unnamed: D106.4 (DOUT), D107.2 (DIN)
unnamed: D107.4 (DOUT), D108.2 (DIN)
unnamed: D108.4 (DOUT), D109.2 (DIN)
unnamed: D109.4 (DOUT), D110.2 (DIN)
unnamed: D110.4 (DOUT), D111.2 (DIN)
unnamed: D111.4 (DOUT), D112.2 (DIN)
unnamed: D112.4 (DOUT), D113.2 (DIN)
unnamed: D113.4 (DOUT), D114.2 (DIN)
unnamed: D114.4 (DOUT), D115.2 (DIN)
unnamed: D115.4 (DOUT), D116.2 (DIN)
unnamed: D116.4 (DOUT), D117.2 (DIN)
unnamed: D117.4 (DOUT), D118.2 (DIN)
unnamed: D118.4 (DOUT), D119.2 (DIN)
unnamed: D120.4 (DOUT), D121.2 (DIN)
unnamed: D121.4 (DOUT), D122.2 (DIN)
unnamed: D122.4 (DOUT), D123.2 (DIN)
unnamed: D123.4 (DOUT), D124.2 (DIN)
unnamed: D124.4 (DOUT), D125.2 (DIN)
unnamed: D125.4 (DOUT), D126.2 (DIN)
unnamed: D126.4 (DOUT), D127.2 (DIN)
unnamed: D127.4 (DOUT), D128.2 (DIN)
unnamed: D128.4 (DOUT), D129.2 (DIN)
unnamed: D129.4 (DOUT), D130.2 (DIN)
unnamed: D130.4 (DOUT), D131.2 (DIN)
unnamed: D131.4 (DOUT), D132.2 (DIN)
unnamed: D133.4 (DOUT), D134.2 (DIN)
unnamed: D134.4 (DOUT), D135.2 (DIN)
unnamed: D135.4 (DOUT), D136.2 (DIN)
unnamed: D136.4 (DOUT), D137.2 (DIN)
unnamed: D137.4 (DOUT), D138.2 (DIN)
unnamed: D138.4 (DOUT), D139.2 (DIN)
unnamed: D139.4 (DOUT), D140.2 (DIN)
unnamed: D140.4 (DOUT), D141.2 (DIN)
unnamed: D141.4 (DOUT), D142.2 (DIN)
unnamed: D142.4 (DOUT), D143.2 (DIN)
unnamed: D143.4 (DOUT), D144.2 (DIN)
unnamed: D144.4 (DOUT), D145.2 (DIN)
unnamed: D146.4 (DOUT), D147.2 (DIN)
unnamed: D147.4 (DOUT), D148.2 (DIN)
unnamed: D148.4 (DOUT), D149.2 (DIN)
unnamed: D149.4 (DOUT), D150.2 (DIN)
unnamed: D150.4 (DOUT), D151.2 (DIN)
unnamed: D151.4 (DOUT), D152.2 (DIN)
unnamed: D152.4 (DOUT), D153.2 (DIN)
unnamed: D153.4 (DOUT), D154.2 (DIN)
unnamed: D154.4 (DOUT), D155.2 (DIN)
unnamed: D155.4 (DOUT), D156.2 (DIN)
unnamed: D158.2 (A), EC3.S1
unnamed: D159.2 (A), EC4.S1
unnamed: D160.2 (A), EC5.S1
unnamed: J1.11, LEDDEBUG1.2, R1.2
ROW0: A1.4 (GPIO2), D1.1 (K), D2.1 (K), D3.1 (K), D4.1 (K), D5.1 (K), D6.1 (K), D7.1 (K), D8.1 (K), D9.1 (K), D10.1 (K), D11.1 (K), D12.1 (K), D13.1 (K), D158.1 (K)
ROW1: A1.5 (GPIO3), D14.1 (K), D15.1 (K), D16.1 (K), D17.1 (K), D18.1 (K), D19.1 (K), D20.1 (K), D21.1 (K), D22.1 (K), D23.1 (K), D24.1 (K), D25.1 (K), D26.1 (K), D75.1 (K)
ROW2: A1.6 (GPIO4), D27.1 (K), D28.1 (K), D29.1 (K), D30.1 (K), D31.1 (K), D32.1 (K), D33.1 (K), D34.1 (K), D35.1 (K), D36.1 (K), D37.1 (K), D38.1 (K), D39.1 (K), D74.1 (K)
ROW3: A1.7 (GPIO5), D40.1 (K), D41.1 (K), D42.1 (K), D43.1 (K), D44.1 (K), D45.1 (K), D46.1 (K), D47.1 (K), D48.1 (K), D49.1 (K), D50.1 (K), D51.1 (K), D52.1 (K), D159.1 (K)
ROW4: A1.9 (GPIO6), D53.1 (K), D54.1 (K), D55.1 (K), D56.1 (K), D57.1 (K), D58.1 (K), D59.1 (K), D60.1 (K), D61.1 (K), D62.1 (K), D63.1 (K), D64.1 (K), D65.1 (K), D160.1 (K)
ROW5: A1.10 (GPIO7), D66.1 (K), D67.1 (K), D68.1 (K), D69.1 (K), D70.1 (K), D71.1 (K), D72.1 (K), D73.1 (K), D77.1 (K), D78.1 (K), D79.1 (K)
RUN: D157.1 (K), D161.1 (K), DEBUG1.2
SCL: A2.7 (GPIO5), J3.5 (SCL), R4.2
SDA: A2.6 (GPIO4), J3.6, R3.2
SLAVEPWR: A2.36 (3V3), J1.7, J1.14, R1.1, R2.2, R3.1, R4.1, R5.1, R6.1, R7.1, R9.1, R10.1, R11.1, R12.1
T_CLK: A2.14 (GPIO10), J1.5
T_CS: A2.17 (GPIO13), J1.4, R6.2
T_INT: A2.19 (GPIO14), J1.1
T_MISO: A2.16 (GPIO12), J1.2
T_MOSI: A2.15 (GPIO11), J1.3
UART0_RX: A1.2 (UART0_RX), A2.1 (UART0_TX)
UART0_TX: A1.1 (UART0_TX), A2.2 (UART0_RX)
V+: J3.4, J4.2

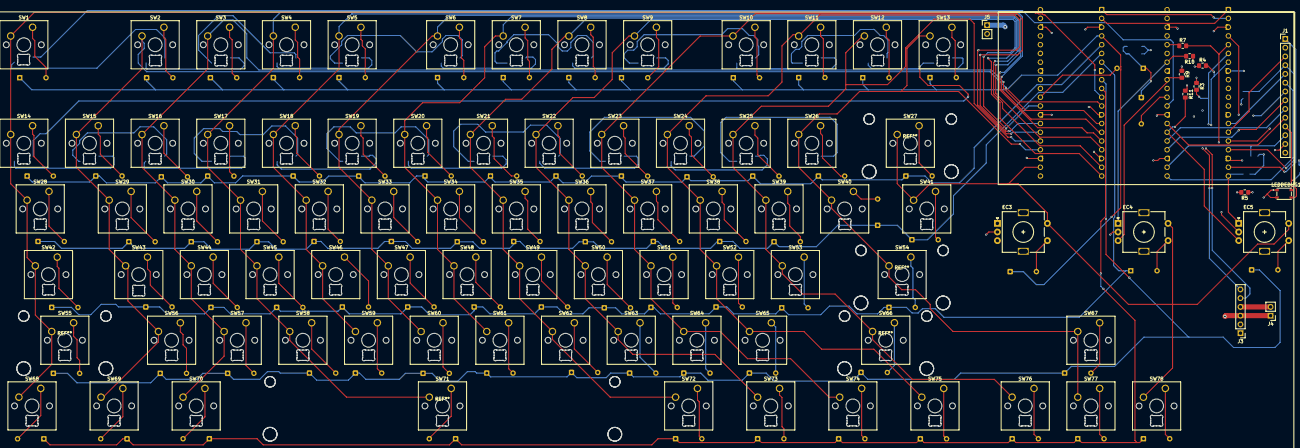
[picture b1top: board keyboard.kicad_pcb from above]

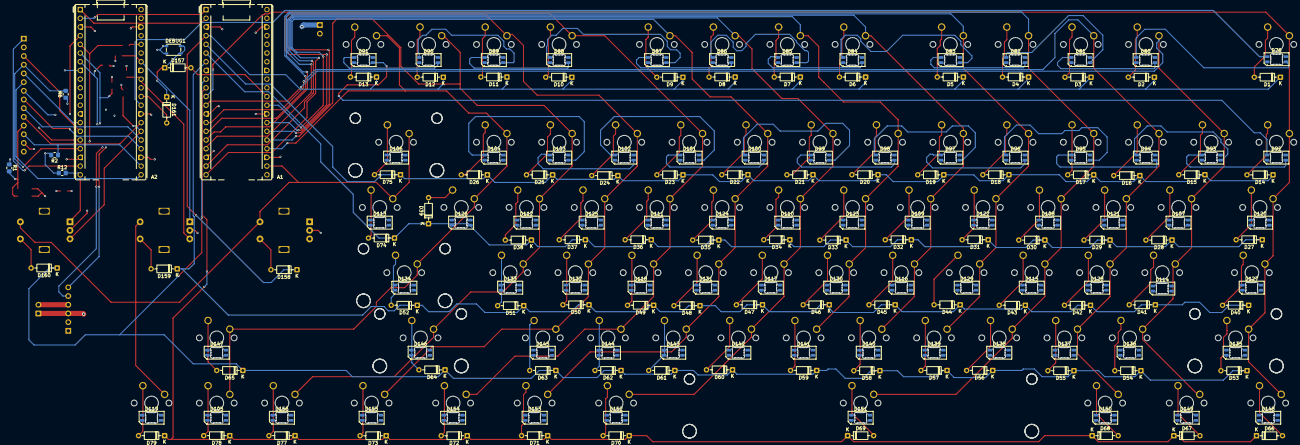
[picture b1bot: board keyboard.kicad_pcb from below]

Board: 4 copper layers, 261 parts (168 on the bottom side), 207 nets.

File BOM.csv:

"Reference","Qty","Value","DNP","Exclude from BOM","Exclude from Board","Footprint","Datasheet"
"A1,A2","2","RaspberryPi_Pico","","","","Module:RaspberryPi_Pico_Common_THT","https://datasheets.raspberrypi.com/pico/pico-datasheet.pdf"
"C1,C2","2","10uF","","","","Capacitor_SMD:C_1206_3216Metric_Pad1.33x1.80mm_HandSolder",""
"C3,C4,C5,C6,C7,C8,C9,C10,C11,C12","10","100nF","","","","Capacitor_SMD:C_0805_2012Metric_Pad1.18x1.45mm_HandSolder",""
"D1,D2,D3,D4,D5,D6,D7,D8,D9,D10,D11,D12,D13,D14,D15,D16,D17,D18,D19,D20,D21,D22,D23,D24,D25,D26,D27,D28,D29,D30,D31,D32,D33,D34,D35,D36,D37,D38,D39,D40,D41,D42,D43,D44,D45,D46,D47,D48,D49,D50,D51,D52,D53,D54,D55,D56,D57,D58,D59,D60,D61,D62,D63,D64,D65,D66,D67,D68,D69,D70,D71,D72,D73,D74,D75,D77,D78,D79,D157,D158,D159,D160,D161","83","D","","","","Diode_THT:D_DO-35_SOD27_P7.62mm_Horizontal",""
"D76,D80,D81,D82,D83,D84,D85,D86,D87,D88,D89,D90,D91,D92,D93,D94,D95,D96,D97,D98,D99,D100,D101,D102,D103,D104,D105,D106,D107,D108,D109,D110,D111,D112,D113,D114,D115,D116,D117,D118,D119,D120,D121,D122,D123,D124,D125,D126,D127,D128,D129,D130,D131,D132,D133,D134,D135,D136,D137,D138,D139,D140,D141,D142,D143,D144,D145,D146,D147,D148,D149,D150,D151,D152,D153,D154,D155,D156","78","SK6812MINI-E","","","","LED_SMD:LED_SK6812MINI-E_3.2x2.8mm_P1.5mm_ReverseMount","https://www.lcsc.com/datasheet/C5149201.pdf"
"DEBUG1,LEDDEBUG1","2","SW_Push","","","","PTS810_SJM_250_SMTR_LFS:SW_PTS810_SJM_250_SMTR_LFS",""
"EC3,EC4,EC5","3","RotaryEncoder_Switch","","","","Rotary_Encoder:RotaryEncoder_Alps_EC11E-Switch_Vertical_H20mm",""
"J1","1","Conn_01x14_Pin","","","","Connector_PinHeader_2.54mm:PinHeader_1x14_P2.54mm_Vertical",""
"J3","1","Conn_01x06_Pin","","","","Connector_PinHeader_2.54mm:PinHeader_1x06_P2.54mm_Vertical",""
"J4,J5","2","Conn_01x02_Pin","","","","Connector_PinHeader_2.54mm:PinHeader_1x02_P2.54mm_Vertical",""
"R1,R2,R5,R6,R7,R9,R10,R11,R12","9","10k","","","","Resistor_SMD:R_0805_2012Metric_Pad1.20x1.40mm_HandSolder",""
"R3,R4","2","4.7k","","","","Resistor_SMD:R_0805_2012Metric_Pad1.20x1.40mm_HandSolder",""
"SW1,SW2,SW3,SW4,SW5,SW6,SW7,SW8,SW9,SW10,SW11,SW12,SW13,SW14,SW15,SW16,SW17,SW18,SW19,SW20,SW21,SW22,SW23,SW24,SW25,SW26,SW29,SW30,SW31,SW32,SW33,SW34,SW35,SW36,SW37,SW38,SW39,SW40,SW43,SW44,SW45,SW46,SW47,SW48,SW49,SW50,SW51,SW52,SW53,SW56,SW57,SW58,SW59,SW60,SW61,SW62,SW63,SW64,SW65,SW67,SW76,SW77,SW78","63","SW_Push","","","","Button_Switch_Keyboard:SW_Cherry_MX_1.00u_PCB",""
"SW27","1","SW_Push","","","","Button_Switch_Keyboard:SW_Cherry_MX_2.00u_PCB",""
"SW28,SW41,SW42","3","SW_Push","","","","Button_Switch_Keyboard:SW_Cherry_MX_1.50u_PCB",""
"SW54,SW55","2","SW_Push","","","","Button_Switch_Keyboard:SW_Cherry_MX_2.25u_PCB",""
"SW66","1","SW_Push","","","","Button_Switch_Keyboard:SW_Cherry_MX_2.75u_PCB",""
"SW68,SW69,SW70,SW72,SW73,SW74,SW75","7","SW_Push","","","","Button_Switch_Keyboard:SW_Cherry_MX_1.25u_PCB",""
"SW71","1","SW_Push","","","","Button_Switch_Keyboard:SW_Cherry_MX_6.25u_PCB",""

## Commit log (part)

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2026-06-01 Finalized PCB files
2026-06-13 CAD_FILES
2026-06-13 QMK_Upload
2026-06-13 Revise README with project details and specifications
    Updated project description and added key features, images, and BOM details.
2026-06-13 Refactor BOM formatting in README.md
    Updated the Bill of Materials (BOM) section to remove extra spaces.
2026-06-13 Fix formatting of key features in README.md
2026-06-13 Fix formatting in README.md
2026-06-13 Revise README to enhance project overview
    Updated project description for clarity and detail.
2026-06-13 Update README.md for improved formatting
    Formatted the README content for better readability.
2026-06-13 Add set_pattern method to total_init class
2026-06-23 added stl files
2026-06-24 Add full render image to README
    Added a full render image to the README.
